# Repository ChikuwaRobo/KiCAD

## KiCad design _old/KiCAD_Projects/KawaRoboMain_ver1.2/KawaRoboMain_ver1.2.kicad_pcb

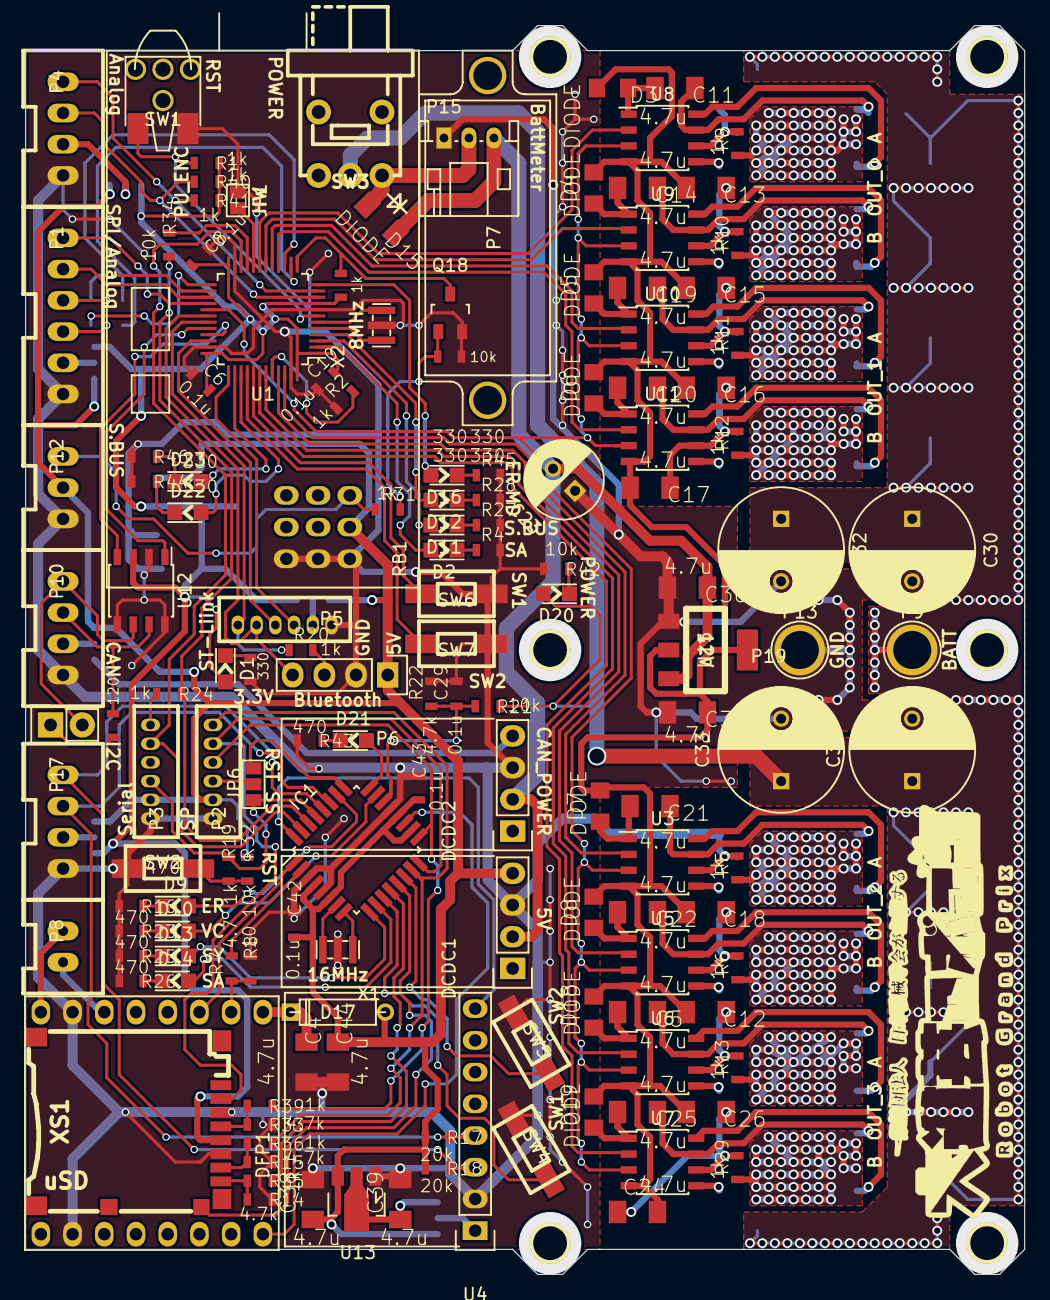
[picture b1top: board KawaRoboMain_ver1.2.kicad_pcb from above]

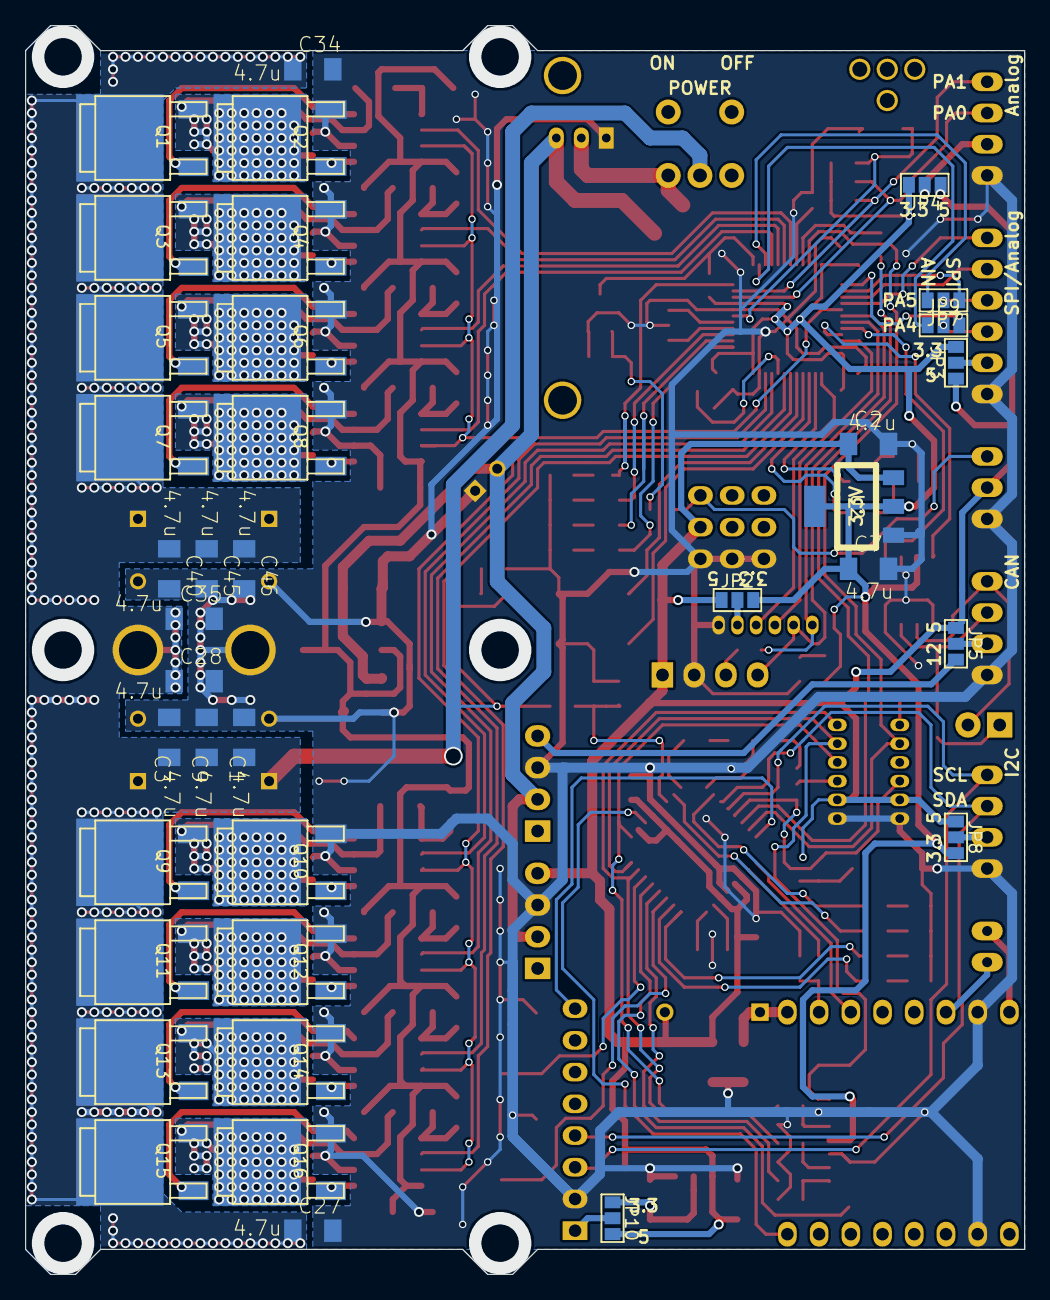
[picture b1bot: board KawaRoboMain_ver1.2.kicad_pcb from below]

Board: 2 copper layers, 80.0 x 100.0 mm, 189 parts (37 on the bottom side), 141 nets.

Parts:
C1, C2, C3, C4, C5, C7, C9, C11, C12, C13, C14, C15, C16, C17, C18, C19, C20, C21, C22, C24, C25, C26, C27, C28, C34, C35, C36, C37, C38, C39, C40, C44, C45, C46: 4.7u; C3216_S
C6, C8, C10, C29, C42, C43: 0.1u; C1608_WP_S
C23: C; C_Radial_D6.3_L11.2_P2.5
C30, C31, C32, C33: 220u; C_Radial_D10_L13_P5
D1, D2, D9, D10, D11, D12, D13, D14, D16, D20, D21, D22, D23: LED; LED_0805
D3, D4, D5, D6, D7, D8, D18, D19: DIODE; C2012
D15: DIODE; C3216_S
D17: DIODE; D3
DCDC1, DCDC2: ChinaDC-DC
DFP1: DFPlayerMini; DFPlayer
IC1: ATMEGA328P-A; TQFP-32_7x7mm_Pitch0.8mm
JP1: JUMPER; GS2
JP2, JP3, JP4, JP5, JP6, JP7, JP8, JP9, JP10: JUMPER3; GS3
P1: CONN_01X06; XA_6T
P2, P3, P5: CONN_01X06; ZH_6T
P4, P10, P17: CONN_01X04; XA_4T
P6: CONN_01X04; Socket_Strip_Straight_1x04
P7: CONN_01X01; V_BattMeter
P8: CONN_01X02; XA_2T
P9, P13: CONN_01X01; 1pin
P11: CONN_01X02; Pin_Header_Straight_1x02
P12: CONN_01X03; XA_3T
P14: CONN_01X01; RGP_R_N
P15: CONN_01X03; Connectors_JST_S3B-PH-K
P19: CONN_01X01; KawaRobo_Headsink_95x35
P21: CONN_01X01; kw_31mm
P22: CONN_01X01; RGP_S_D
Q1, Q2, Q3, Q4, Q5, Q6, Q7, Q8, Q9, Q10, Q11, Q12, Q13, Q14, Q15, Q16: MOSFET_N; SOT-428_GDS_compact
Q18: MOSFET_N; SOT-23_Handsoldering
R1, R2, R5, R6, R9, R10, R11, R12, R13, R19, R20, R24, R29, R31, R35, R36, R38, R39, R40, R41: 1k; C1608_WP_S
R3, R4, R27, R28, R44, R45, R46: 330; C1608_WP_S
R7: 4.7; C1608_WP_S
R8: 10; C1608_WP_S
R14, R15, R22, R33: 4.7k; C1608_WP_S
R16, R23, R25, R26, R43: 470; C1608_WP_S
R17, R18: 20k; C1608_WP_S
R21, R32, R34, R37, R42: 10k; C1608_WP_S
R30: 120; C1608_WP_S
RB1: R3006SB
SW1: SW_PUSH; ESE22MH
SW2, SW4, SW5, SW6, SW7: SW_PUSH; RP_SMD_Button
SW3: SWITCH_INV; RSpro_slide_side
U1: STM32F103_48; LQFP-48_7x7mm_Pitch0.5mm
U2: NCP1117ST33T3G; SOT-223_reg
U3, U5, U6, U7, U8, U9, U10, U11: NCP5359; SOIC-8_3.9x4.9mm_Pitch1.27mm_S
U4: MPU6050; MPU-6050
U12: MAX3051; SOIC-8_3.9x4.9mm_Pitch1.27mm_S
U13: NCP1117ST33T3G; SOT89-3_Housing
U15: NCP1117ST12T3G; SOT-223_reg
X1, X2: ceralock; Resonator_3×1.3mm
XS1: uSD; microsd_socket

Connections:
+3.3V: C6.2, C7.1, C8.2, C10.2, D1.1, JP2.3, JP3.3, JP4.3, JP8.3, R1.1, R38.2, R40.1, R41.1, U1.1, U1.9, U1.24, U1.36, U1.48, U2.2, U12.3, XS1.4
+5V: C2.1, C38.1, C42.2, C43.2, C44.1, D17.2, DCDC1.4, IC1.4, IC1.6, IC1.18, IC1.20, JP2.1, JP3.1, JP4.1, JP5.1, JP8.1, JP10.3, P2.2, P3.2, P6.1, P12.2, R17.2, R18.2, R32.1, RB1.2, U2.3, U13.3
+12V: DCDC2.4, JP5.3
+BATT: C1.1, C3.1, C9.1, C27.1, C28.1, C30.1, C31.1, C32.1, C33.1, C34.1, C35.1, C40.1, C45.1, C46.1, D20.1, P9.1, Q1.D, Q3.D, Q5.D, Q7.D, Q9.D, Q11.D, Q13.D, Q15.D, R21.1, SW3.2
/AIN_1: JP9.1, U1.14
/AIN_2: JP7.3, U1.15
/AT_LED1: D13.1, IC1.9
/AT_LED2: D14.1, IC1.10
/AT_LED3: D9.1, IC1.26
/AT_LED4: D10.1, IC1.23
/AT_LED5: D21.1, IC1.24
/AT_RST: IC1.29, JP6.1, P3.3, R19.1
/AT_RX: IC1.30, R24.1, R34.2
/AT_SW1: IC1.11, SW4.2
/AT_SW2: IC1.14, SW5.2
/AT_TX: IC1.31, P3.5, U1.22
/BOOT0: R2.2, U1.44
/CAN_H: P10.3, R30.1, U12.7
/CAN_L: P10.4, P11.2, U12.6
/CAN_RX: U1.33, U12.4
/CAN_TX: U1.32, U12.1
/DFP_BUSY: DFP1.16, IC1.19
/DFP_RX: IC1.2, R7.2
/DFP_TX: DFP1.3, IC1.1
/EX_SS: IC1.25, JP6.3
/GD_12V: C12.2, C13.2, C15.2, C16.2, C17.2, C18.2, C24.2, C26.2, C37.1, D3.2, D4.2, D5.2, D6.2, D7.2, D8.2, D18.2, D19.2, U3.4, U5.4, U6.4, U7.4, U8.4, U9.4, U10.4, U11.4, U15.2
/HW_OPT: JP1.2, U1.20
/I2C_SCL: IC1.28, P17.4, R18.1, U4.3
/I2C_SDA: IC1.27, P17.3, R17.1, U4.4
/INT0: IC1.32, U4.8
/LOGIC_BATT: C23.2, C36.1, D15.1, DCDC1.2, DCDC2.2, P15.3, U15.3
/MPU_3.3V: C39.1, JP10.1, U13.2
/NRST: R1.2, SW1.2, U1.7
/OSC_IN: U1.5, X2.1
/OSC_OUT: U1.6, X2.3
/OUT_0_A: C11.1, Q1.S, Q2.D, R9.1, U8.7
/OUT_0_B: C14.1, Q3.S, Q4.D, R10.1, U9.7
/OUT_1_A: C19.1, Q5.S, Q6.D, R11.1, U10.7
/OUT_1_B: C20.1, Q7.S, Q8.D, R12.1, U11.7
/OUT_2_A: C21.1, Q9.S, Q10.D, R5.1, U3.7
/OUT_2_B: C22.1, Q11.S, Q12.D, R6.1, U5.7
/OUT_3_A: C5.1, Q13.S, Q14.D, R13.1, U6.7
/OUT_3_B: C25.1, Q15.S, Q16.D, R29.1, U7.7
/POT_1: P4.3, R40.2, U1.10
/POT_2: P4.4, R41.2, U1.11
/PWM_0_A: U1.19, U8.2
/PWM_0_B: U1.18, U9.2
/PWM_1_A: U1.17, U10.2
/PWM_1_B: U1.16, U11.2
/PWM_2_A: U1.46, U3.2
/PWM_2_B: U1.45, U5.2
/PWM_3_A: U1.43, U6.2
/PWM_3_B: U1.42, U7.2
/SBUS: Q18.D, R38.1, U1.13
/SD_CD: IC1.13, XS1.CD2
/SD_SS: IC1.12, R35.1
/SPI_MISO: IC1.16, P2.5, XS1.7
/SPI_MOSI: IC1.15, P2.6, R36.1
/SPI_SCK: IC1.17, P2.4, R39.1
/STM_LED1: D2.1, U1.2
/STM_LED2: D11.1, U1.3
/STM_LED3: D12.1, U1.4
/STM_LED4: D16.1, U1.12
/STM_LED5: D22.1, U1.39
/STM_LED6: D23.1, U1.38
/STM_MISO: P1.5, U1.27
/STM_MOSI: P1.6, U1.28
/STM_SCK: JP7.1, U1.26
/STM_SW1: SW6.2, U1.41
/STM_SW2: SW7.2, U1.40
/STM_~SS0: JP9.3, U1.25
/SWCLK: P5.3, U1.37
/SWDIO: P5.4, U1.34
/USART_RX: P5.6, R20.1, U1.31
/USART_TX: P5.5, P6.4, U1.30
/batt_voltage: C29.1, IC1.22, R21.2, R22.1
/~SD: U1.29, U3.3, U5.3, U6.3, U7.3, U8.3, U9.3, U10.3, U11.3
GND: C1.2, C2.2, C3.2, C4.2, C6.1, C7.2, C8.1, C9.2, C10.1, C12.1, C13.1, C15.1, C16.1, C17.1, C18.1, C23.1, C24.1, C26.1, C27.2, C28.2, C29.2, C30.2, C31.2, C32.2, C33.2, C34.2, C35.2, C36.2, C37.2, C38.2, C39.2, C40.2, C42.1, C43.1, C44.2, C45.2, C46.2, DCDC1.3, DCDC2.3, DFP1.7, DFP1.10, IC1.3, IC1.5, IC1.21, JP1.1, P1.1, P2.1, P3.1, P4.1, P5.1, P6.2, P10.1, P12.1, P13.1, P15.1, P17.1, Q2.S, Q4.S, Q6.S, Q8.S, Q10.S, Q12.S, Q14.S, Q16.S, Q18.S, R2.1, R3.2, R4.2, R5.2, R6.2, R8.1, R9.2, R10.2, R11.2, R12.2, R13.2, R14.1, R15.1, R16.2, R22.2, R23.2, R25.2, R26.2, R27.2, R28.2, R29.2, R33.1, R37.1, R42.2, R43.2, R44.2, R45.2, R46.2, RB1.1, RB1.4, RB1.7, SW1.1, SW2.1, SW4.1, SW5.1, SW6.1, SW7.1, U1.8, U1.23, U1.35, U1.47, U2.1, U3.6, U4.2, U5.6, U6.6, U7.6, U8.6, U9.6, U10.6, U11.6, U12.2, U12.5, U12.8, U13.1, U15.1, X1.2, X2.2, XS1.3, XS1.6
unnamed: C4.1, D17.1, DFP1.1
unnamed: C5.2, D18.1, U6.1
unnamed: C11.2, D3.1, U8.1
unnamed: C14.2, D4.1, U9.1
unnamed: C19.2, D5.1, U10.1
unnamed: C20.2, D6.1, U11.1
unnamed: C21.2, D7.1, U3.1
unnamed: C22.2, D8.1, U5.1
unnamed: C25.2, D19.1, U7.1
unnamed: D1.2, R3.1
unnamed: D2.2, R4.1
unnamed: D9.2, R16.1
unnamed: D10.2, R23.1
unnamed: D11.2, R27.1
unnamed: D12.2, R28.1
unnamed: D13.2, R25.1
unnamed: D14.2, R26.1
unnamed: D15.2, P15.2, SW3.3
unnamed: D16.2, R45.1
unnamed: D20.2, R42.1
unnamed: D21.2, R43.1
unnamed: D22.2, R44.1
unnamed: D23.2, R46.1
unnamed: DFP1.2, R7.1, R8.2
unnamed: DFP1.6, P8.1
unnamed: DFP1.8, P8.2
unnamed: IC1.7, X1.3
unnamed: IC1.8, X1.1
unnamed: JP2.2, P5.2
unnamed: JP3.2, P1.2
unnamed: JP4.2, P4.2
unnamed: JP5.2, P10.2
unnamed: JP6.2, P2.3
unnamed: JP7.2, P1.4
unnamed: JP8.2, P17.2
unnamed: JP9.2, P1.3
unnamed: JP10.2, U4.1
unnamed: P3.6, R24.2
unnamed: P6.3, R20.2
unnamed: P11.1, R30.2
unnamed: P12.3, R31.1, RB1.3
unnamed: Q1.G, U8.8
unnamed: Q2.G, U8.5
unnamed: Q3.G, U9.8
unnamed: Q4.G, U9.5
unnamed: Q5.G, U10.8
unnamed: Q6.G, U10.5
unnamed: Q7.G, U11.8
unnamed: Q8.G, U11.5
unnamed: Q9.G, U3.8
unnamed: Q10.G, U3.5
unnamed: Q11.G, U5.8
unnamed: Q12.G, U5.5
unnamed: Q13.G, U6.8
unnamed: Q14.G, U6.5
unnamed: Q15.G, U7.8
unnamed: Q16.G, U7.5
unnamed: Q18.G, R31.2, R37.2
unnamed: R14.2, R35.2, XS1.1
unnamed: R15.2, R36.2, XS1.2
unnamed: R19.2, R32.2, SW2.2
unnamed: R33.2, R39.2, XS1.5
unnamed: R34.1, U1.21

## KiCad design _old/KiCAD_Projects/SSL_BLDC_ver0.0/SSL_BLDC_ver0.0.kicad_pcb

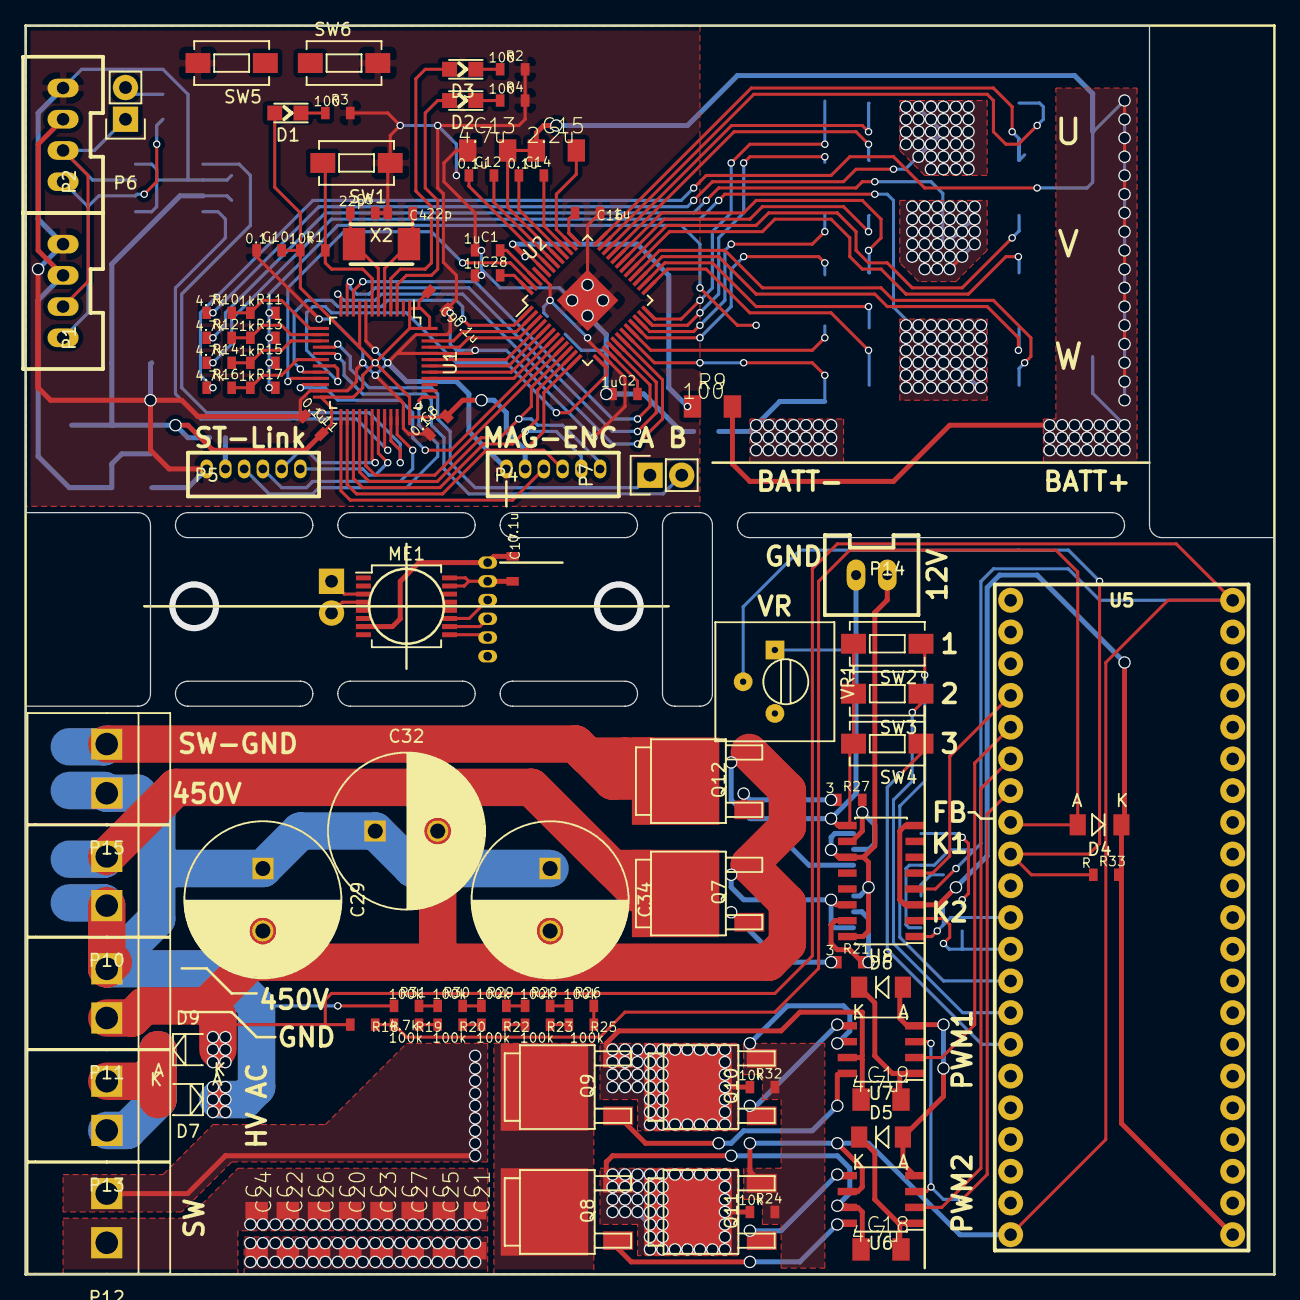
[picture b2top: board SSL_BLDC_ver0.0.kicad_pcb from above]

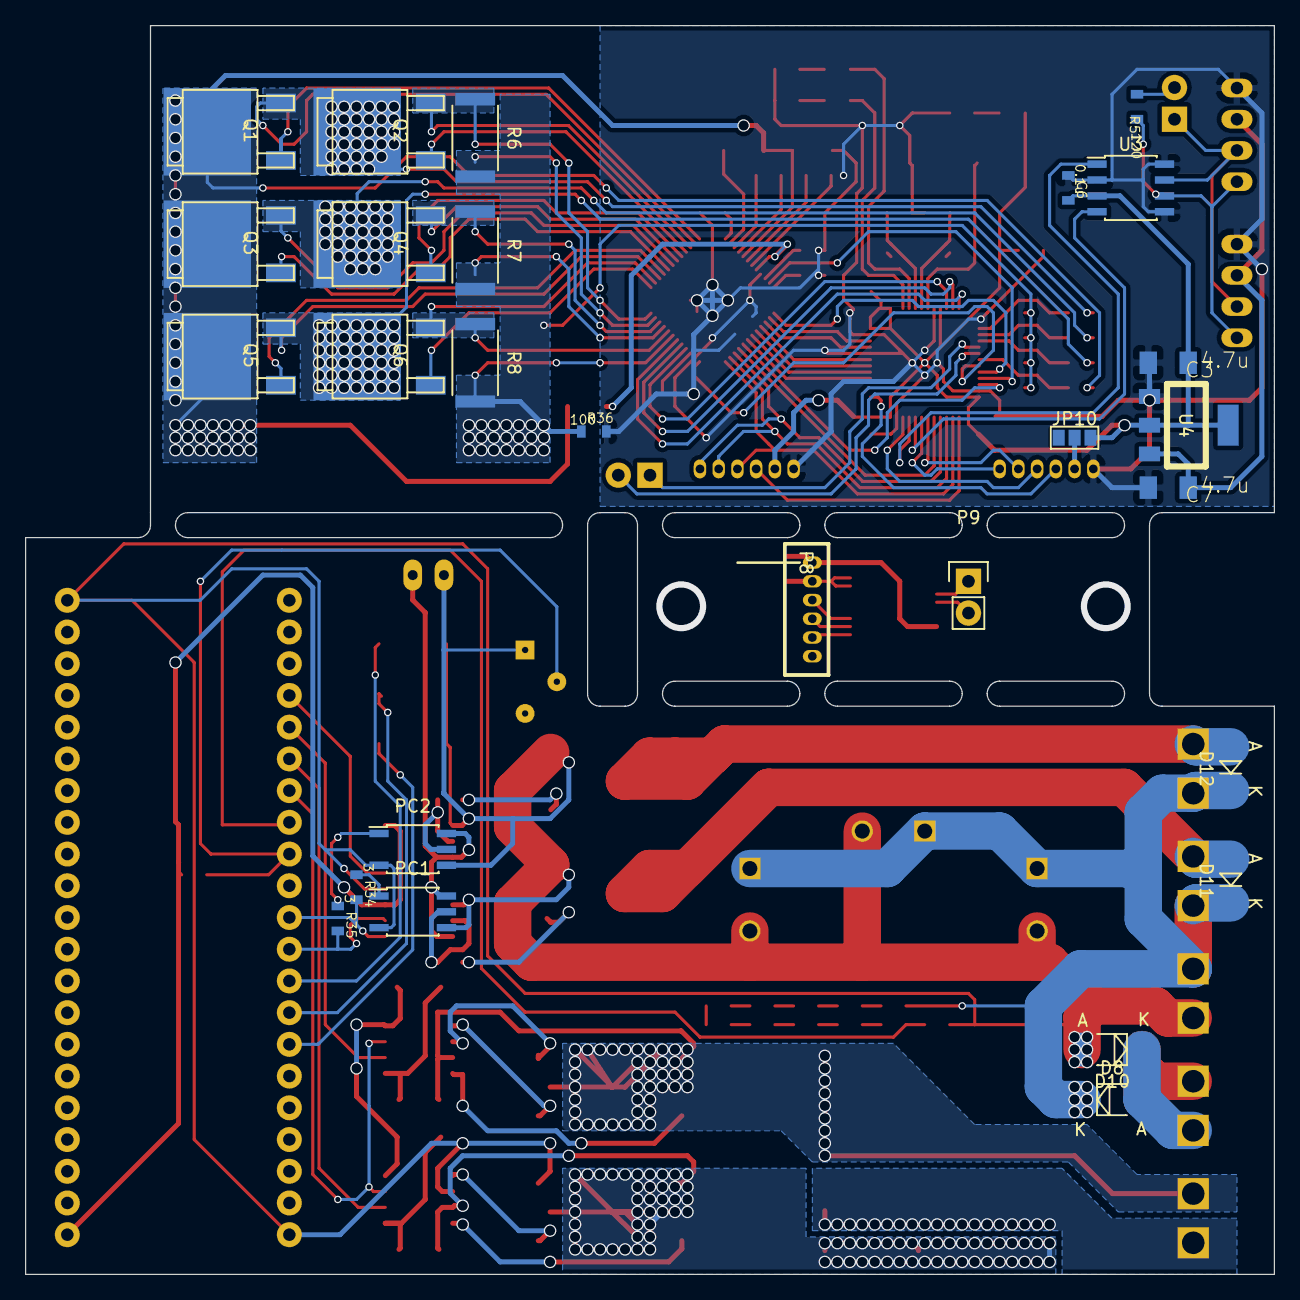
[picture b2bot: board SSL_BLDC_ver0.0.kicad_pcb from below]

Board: 2 copper layers, 100.0 x 100.0 mm, 125 parts (27 on the bottom side), 123 nets.

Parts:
C1, C2, C16, C28: 1u; C1608_WP_S
C3, C7, C13, C18, C19: 4.7u; C3216_S
C4, C5: 22p; C1608_WP_S
C6, C8, C9, C10, C11, C12, C14, C17: 0.1u; C1608_WP_S
C15: 2.2u; C3216_S
C20, C21, C22, C23, C24, C25, C26, C27: C; C3216_S
C29, C32, C34: C; C_Radial_D12.5_L25_P5
D1, D2, D3: LED; LED_0805
D4, D5, D6, D11, D12: DIODE; MiniMELF_Standard
D7, D8, D9, D10: DIODE; MELF_Standard
JP10: JUMPER3; GS3
ME1: AS504x; SSOP-16_5.3x6.2mm_Pitch0.65mm
P1, P2: CONN_01X04; XA_4T
P4, P5, P8: CONN_01X06; ZH_6T
P6, P7, P9: CONN_01X02; Pin_Header_Straight_1x02
P10, P11, P12, P13, P15: CONN_01X02; GTK2400-V2
P14: CONN_01X02; XA_2T
PC1, PC2: TLP117; SOIC-5_3.9x4.9mm_Pitch1.27mm
Q1, Q2, Q3, Q4, Q5, Q6, Q7, Q8, Q9, Q10, Q11, Q12: MOSFET_N; SOT-428_GDS_compact
R1, R24, R32: 10k; C1608_WP_S
R2, R3, R4, R36: 100; C1608_WP_S
R5: 120; C1608_WP_S
R6, R7, R8: 10m; R_2512
R9: 100; C3216_S
R10, R12, R14, R16, R18: 4.7k; C1608_WP_S
R11, R13, R15, R17: 1k; C1608_WP_S
R19, R20, R22, R23, R25, R26, R28, R29, R30, R31: 100k; C1608_WP_S
R21, R27, R34, R35: 3; C1608_WP_S
R33: R; C1608_WP_S
SW1, SW2, SW3, SW4, SW5, SW6: SW_PUSH; SW_SPST_EVQPE1
U1: STM32F103_48; LQFP-48_7x7mm_Pitch0.5mm
U2: DRV8305; TQFP-48-1EP_7x7mm_Pitch0.5mm
U3: MAX3051; SOIC-8_3.9x4.9mm_Pitch1.27mm
U4: NCP1117ST50T3G; SOT-223_reg
U5: F103mini_Ver2.0; F103mini_ver2.0
U6, U7: NCP5359; SOIC-8_3.9x4.9mm_Pitch1.27mm
U8: SI8275; SOIC-16_3.9x9.9mm_Pitch1.27mm
VR1: VR; Potentiometer_Trimmer-Suntan-TSR-3386P
X2: CRYSTAL; ABM3_2pads

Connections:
+3.3V: C3.1, C6.2, C8.2, C9.2, C10.2, C11.2, D1.1, JP10.3, P4.2, R1.1, U1.1, U1.9, U1.24, U1.36, U1.48, U3.3, U4.2
+3.3VP: D4.1, R33.2, U5.22, U8.3, U8.8
+5V: C7.1, P1.2, P2.2, U4.3
+12V: D5.2, D6.2, U6.4, U7.4
+BATT: C13.2, C15.1, Q1.D, Q3.D, Q5.D, R9.2, R16.1, U2.41
/AS_3.3V: C17.2, ME1.15, ME1.16, P8.2
/AS_ENC_A: ME1.3, P9.1
/AS_ENC_B: ME1.4, P9.2
/AS_GND: C17.1, ME1.7, P8.1
/AS_SPI_MISO: ME1.9, P8.5
/AS_SPI_NSS_ENC: ME1.11, P8.3
/AS_SPI_SCK: ME1.10, P8.4
/BATT_V: R16.2, R17.1, U1.18
/CAN_H: P1.3, P2.3, P6.1, U3.7
/CAN_L: P1.4, P2.4, R5.1, U3.6
/CAN_RX: U1.32, U3.4
/CAN_TX: U1.33, U3.1
/CS_U: U1.10, U2.16
/CS_V: U1.11, U2.17
/CS_W: U1.12, U2.18
/ENC_A: P7.1, U1.16
/ENC_B: P7.2, U1.17
/GATE_U_H: Q1.G, U2.36
/GATE_U_L: Q2.G, U2.33
/GATE_V_H: Q3.G, U2.29
/GATE_V_L: Q4.G, U2.32
/GATE_W_H: Q5.G, U2.28
/GATE_W_L: Q6.G, U2.25
/GD_EN: U1.20, U2.1
/GD_WAKE: U1.21, U2.47
/LED_A: D2.1, U1.3
/LED_B: D3.1, U1.4
/NRST: R1.2, SW1.2, U1.7
/OSC_IN: C4.1, U1.5, X2.1
/OSC_OUT: C5.1, U1.6, X2.2
/OUT_U: Q1.S, Q2.D, R10.1, U2.35
/OUT_V: Q3.S, Q4.D, R12.1, U2.30
/OUT_W: Q5.S, Q6.D, R14.1, U2.27
/PWGD: U1.19, U2.13
/PWM_U_H: U1.46, U2.2
/PWM_U_L: U1.45, U2.3
/PWM_V_H: U1.43, U2.4
/PWM_V_L: U1.42, U2.5
/PWM_W_H: U1.41, U2.6
/PWM_W_L: U1.40, U2.7
/SPI_MISO: P4.5, U1.27, U2.11
/SPI_MOSI: P4.6, U1.28, U2.10
/SPI_NSS_ENC: P4.3, U1.25
/SPI_NSS_GD: U1.29, U2.9
/SPI_SCK: P4.4, U1.26, U2.12
/SWCLK: P5.3, U1.37
/SWDIO: P5.4, U1.34
/S_U_L: Q2.S, R6.1, U2.24, U2.34
/S_V_L: Q4.S, R7.1, U2.22, U2.31
/S_W_L: Q6.S, R8.1, U2.20, U2.26
/USART_RX: P5.6, U1.31
/USART_TX: P5.5, U1.30
/VS_U: R10.2, R11.1, U1.13
/VS_V: R12.2, R13.1, U1.14
/VS_W: R14.2, R15.1, U1.15
/boost/450V: C29.1, C32.1, C34.1, D7.1, D8.1, D11.1, D12.1, P10.1, P11.2, P15.1, R31.1
/boost/FB: D4.2, R18.1, R19.2, U5.8
/boost/GD_EN: U5.4, U8.5
/boost/GD_EN_NCP: U5.7, U6.3, U7.3
/boost/GD_PWM1: U5.5, U7.2
/boost/GD_PWM2: U5.6, U6.2
/boost/KICK_GATE1: PC1.5, R21.2, U8.15
/boost/KICK_GATE2: PC2.5, R27.2, U8.10
/boost/Kick1: R34.2, U5.11, U8.1
/boost/Kick2: R35.2, U5.12, U8.2
/boost/SW1: C19.1, P12.2, Q9.S, Q10.D, R32.1, U7.7
/boost/SW2: C20.1, C21.1, C22.1, C23.1, C24.1, C25.1, C26.1, C27.1, P12.1
/boost/analog: R33.1, U5.9, VR1.2
/boost/boostBATT: Q8.D, Q9.D
/boost/pw12V: P14.2, PC1.6, PC2.6, U8.11, U8.16
/boost/userSW1: SW2.1, U5.13
/boost/userSW2: SW3.1, U5.14
/boost/userSW3: SW4.1, U5.15
/nFALUT: U1.22, U2.8
DGND: C29.2, C32.2, C34.2, D9.2, D10.2, P11.1, P14.1, PC1.3, PC1.4, PC2.3, PC2.4, Q7.S, Q10.S, Q11.S, Q12.S, R18.2, R24.2, R32.2, SW2.2, SW3.2, SW4.2, U5.21, U5.42, U6.6, U7.6, U8.4, U8.9, U8.14, VR1.1
GND: C1.1, C2.1, C3.2, C4.2, C5.2, C6.1, C7.2, C8.1, C9.1, C10.1, C11.1, C13.1, C16.1, C28.1, P1.1, P2.1, P4.1, P5.1, R2.2, R3.2, R4.2, R36.2, SW1.1, SW5.2, SW6.2, U1.8, U1.23, U1.35, U1.44, U1.47, U2.14, U2.45, U2.49, U3.2, U3.5, U3.8, U4.1
GNDPWR: R6.2, R7.2, R8.2, R11.2, R13.2, R15.2, R17.2, R36.1, U2.19, U2.21, U2.23
unnamed: C1.2, U2.46
unnamed: C2.2, U2.15
unnamed: C12.1, U2.43
unnamed: C12.2, U2.42
unnamed: C14.1, U2.40
unnamed: C14.2, U2.39
unnamed: C15.2, U2.38
unnamed: C16.2, U2.37
unnamed: C18.1, C20.2, C21.2, C22.2, C23.2, C24.2, C25.2, C26.2, C27.2, Q8.S, Q11.D, R24.1, U6.7
unnamed: C18.2, D5.1, U6.1
unnamed: C19.2, D6.1, U7.1
unnamed: C28.2, U2.48
unnamed: D1.2, R3.1
unnamed: D2.2, R4.1
unnamed: D3.2, R2.1
unnamed: D7.2, D9.1, P13.2
unnamed: D8.2, D10.1, P13.1
unnamed: D11.2, P10.2, Q7.D
unnamed: D12.2, P15.2, Q12.D
unnamed: JP10.2, P5.2
unnamed: P6.2, R5.2
unnamed: PC1.1, R34.1
unnamed: PC2.1, R35.1
unnamed: Q7.G, R21.1
unnamed: Q8.G, U6.8
unnamed: Q9.G, U7.8
unnamed: Q10.G, U7.5
unnamed: Q11.G, U6.5
unnamed: Q12.G, R27.1
unnamed: R9.1, U2.44
unnamed: R19.1, R20.2
unnamed: R20.1, R22.2
unnamed: R22.1, R23.2
unnamed: R23.1, R25.2
unnamed: R25.1, R26.2
unnamed: R26.1, R28.2
unnamed: R28.1, R29.2
unnamed: R29.1, R30.2
unnamed: R30.1, R31.2
unnamed: SW5.1, U1.39
unnamed: SW6.1, U1.38

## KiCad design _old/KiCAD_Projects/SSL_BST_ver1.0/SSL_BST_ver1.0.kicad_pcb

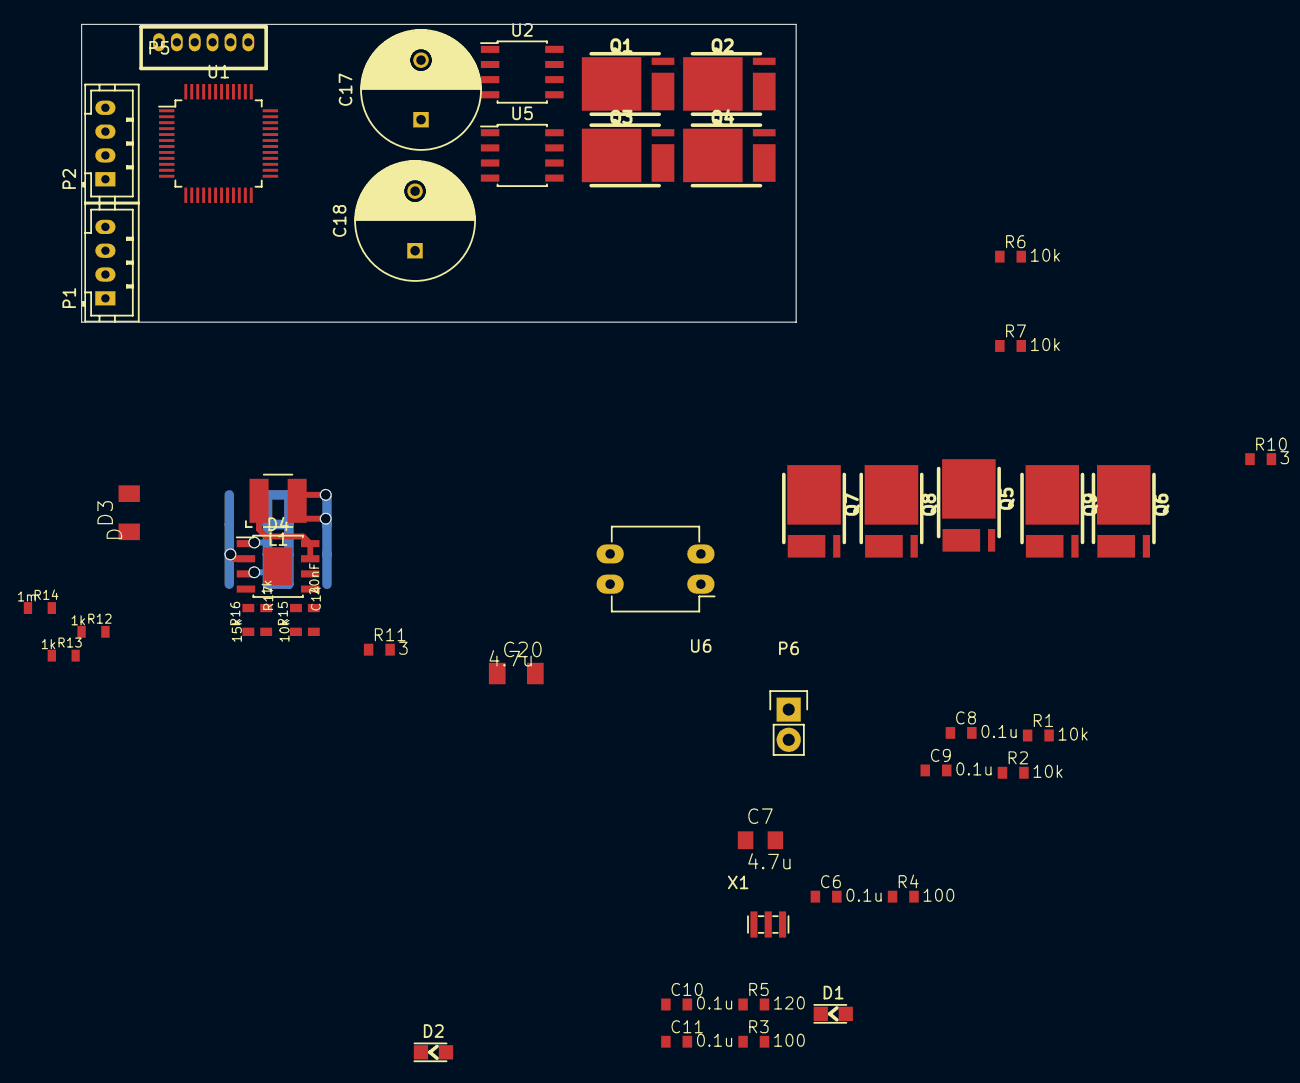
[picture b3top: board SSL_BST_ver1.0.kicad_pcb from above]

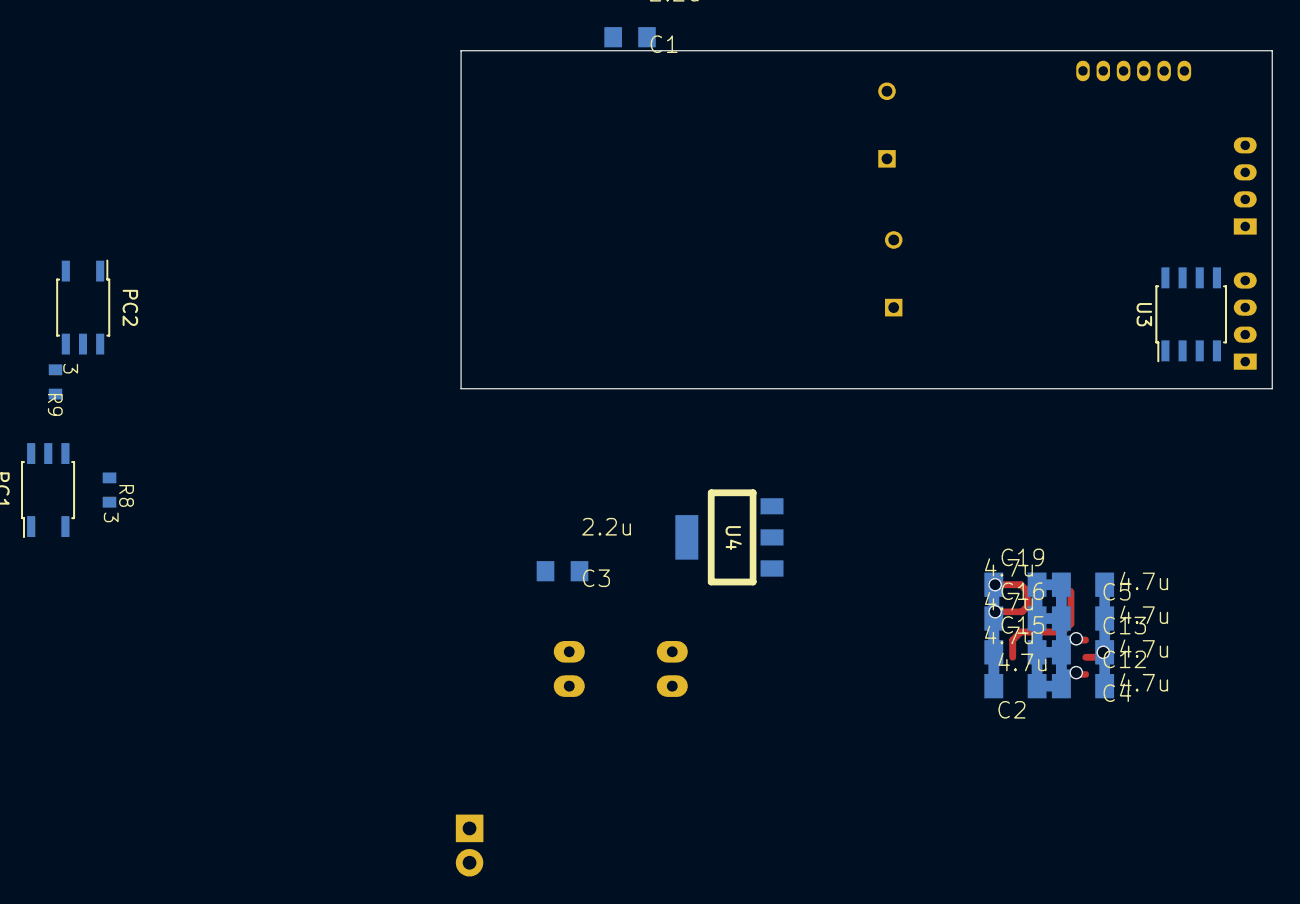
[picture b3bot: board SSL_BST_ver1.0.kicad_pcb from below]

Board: 2 copper layers, 60.0 x 25.0 mm, 64 parts (16 on the bottom side), 42 nets.

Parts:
C1, C3: 2.2u; C2012
C2, C4, C5, C12, C13, C15, C16, C19, C20: 4.7u; C3216_S
C6, C8, C9, C10, C11: 0.1u; C1608_WP
C7: 4.7u; C2012
C14: 20nF; C1608_WP_S
C17, C18: 470u; C_Radial_D10_L13_P5
D1, D2: LED; LED_0805
D3: D; C3216_S
D4: BD9C601EFJ; SOIC-8_3.9x4.9mm_Pitch1.27mm
L1: 3.3uH; NR4018
P1, P2: CONN_01X04; Connectors_JST_B4B-PH-K
P5: CONN_01X06; ZH_6T
P6: CONN_01X02; Pin_Header_Straight_1x02
PC1, PC2: TLP117; SOIC-5_3.9x4.9mm_Pitch1.27mm
Q1, Q2, Q3, Q4, Q5: Q_NMOS_GDS; DFN56
Q6, Q7, Q8, Q9: Q_PMOS_GDS; DFN56
R1, R2, R6, R7: 10k; C1608_WP
R3, R4: 100; C1608_WP
R5: 120; C1608_WP
R8, R9, R10, R11: 3; C1608_WP
R12, R13, R17: 1k; C1608_WP_S
R14: 1m; C1608_WP_S
R15: 10k; C1608_WP_S
R16: 15k; C1608_WP_S
U1: STM32F103_48; LQFP-48_7x7mm_Pitch0.5mm
U2, U5: NCP5359; SOIC-8_3.9x4.9mm_Pitch1.27mm
U3: MAX3051; SOIC-8_3.9x4.9mm_Pitch1.27mm
U4: NCP1117ST50T3G; SOT-223_reg
U6: OPTO-TRANSISTOR4; DIP-4_W7.62mm_LongPads
X1: ceralock; Resonator_3×1.3mm

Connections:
+3.3V: C6.2, C7.1, C8.2, C9.2, C10.2, D1.1, R1.1, U1.9, U1.24, U1.36, U1.48, U3.3, U4.2
+12V: C2.1, C15.1, C16.1, C19.1, C20.1, L1.2, R16.1, U2.1, U2.4, U4.3, U5.1, U5.4
+BATT: D3.2, R12.2, R14.2
/BOOT0: R2.2, U1.44
/CAN_H: P1.3, P2.3, P6.1, U3.7
/CAN_L: P1.4, P2.4, R5.1, U3.6
/CAN_RX: U1.32, U3.4
/CAN_TX: U1.33, U3.1
/CS_N: Q6.3, Q7.3, Q8.3, Q9.3, R14.1
/GD_12V: PC1.6, PC2.6
/NCP_EN: U2.3, U5.3
/NRST: R1.2, U1.7
/OSC_IN: U1.5, X1.1
/OSC_OUT: U1.6, X1.3
/OUT_EN: Q5.1, R13.2
/PW_OUT: C17.1, C18.1, Q1.2, Q3.2, Q6.2, Q7.2, Q8.2, Q9.2
/SW1: Q1.3, Q2.2, R6.1, U2.7
/SWCLK: P5.3, U1.37
/SWDIO: P5.4, U1.34
/USART_RX: P5.6, U1.31
/USART_TX: P5.5, U1.30
GND: C2.2, C4.2, C5.2, C6.1, C7.2, C8.1, C9.1, C10.1, C11.1, C12.2, C13.2, C14.2, C15.2, C16.2, C19.2, C20.2, D4.1, D4.3, P1.1, P2.1, P5.1, PC1.3, PC2.3, Q2.3, Q4.3, Q5.3, R3.2, R4.2, R6.2, R7.2, R13.1, R17.2, U1.8, U1.23, U1.35, U2.6, U3.2, U3.5, U3.8, U4.1, U5.6, X1.2
GNDPWR: C17.2, C18.2, PC1.4, PC2.4
unnamed: C4.1, C5.1, C12.1, C13.1, D3.1, D4.2
unnamed: C14.1, R15.1
unnamed: D1.2, R3.1
unnamed: D2.2, R4.1
unnamed: D4.4, R16.2, R17.1
unnamed: D4.5, R15.2
unnamed: D4.7, D4.8, L1.1
unnamed: P1.2, P2.2
unnamed: P6.2, R5.2
unnamed: PC1.1, R10.1
unnamed: PC1.5, R8.2
unnamed: PC2.1, R11.1
unnamed: PC2.5, R9.2
unnamed: Q1.1, U2.8
unnamed: Q2.1, U2.5
unnamed: Q3.1, U5.8
unnamed: Q3.3, Q4.2, R7.1, U5.7
unnamed: Q4.1, U5.5
unnamed: Q5.2, Q6.1, Q7.1, Q8.1, Q9.1, R12.1

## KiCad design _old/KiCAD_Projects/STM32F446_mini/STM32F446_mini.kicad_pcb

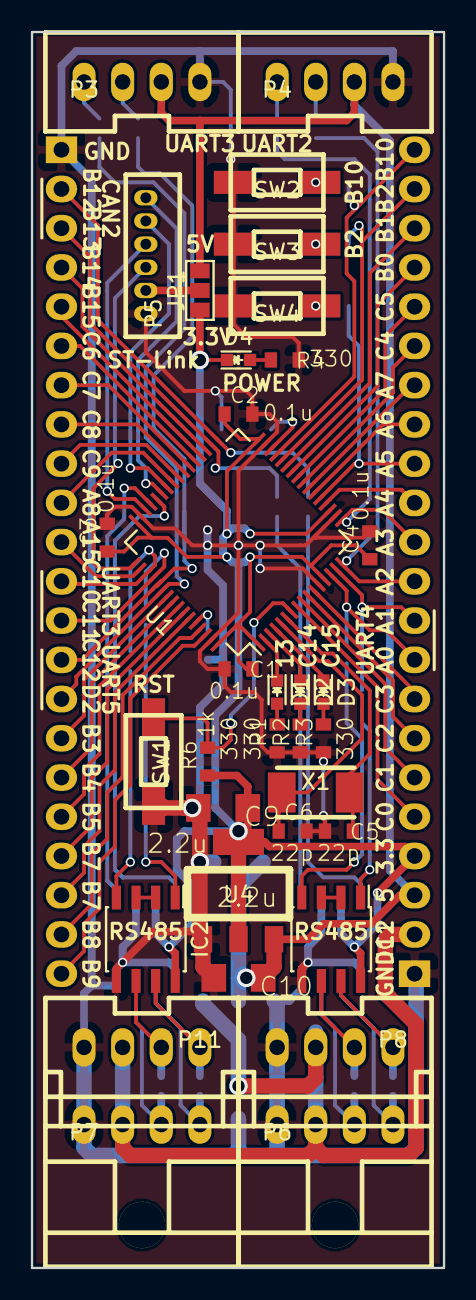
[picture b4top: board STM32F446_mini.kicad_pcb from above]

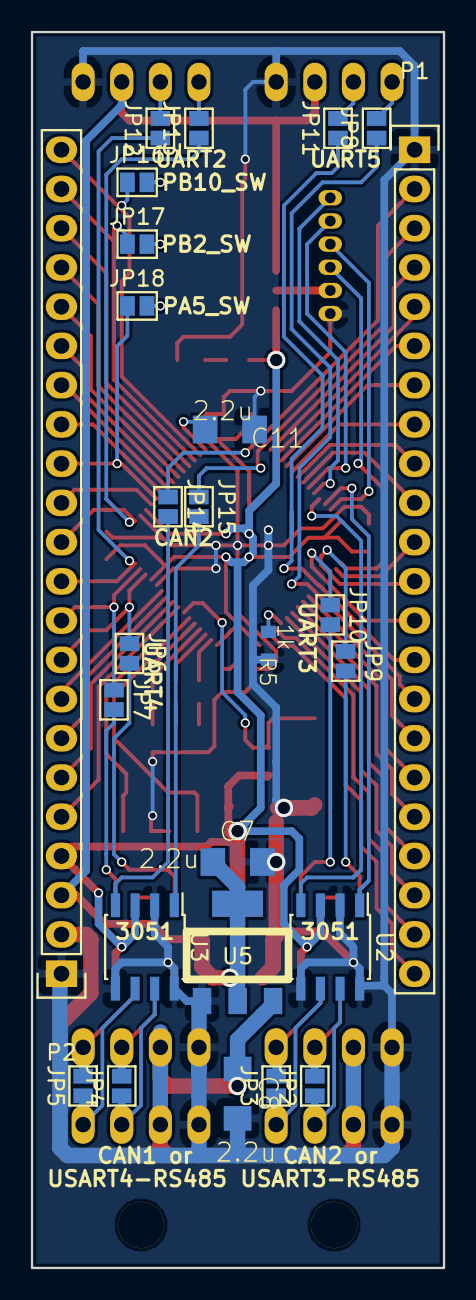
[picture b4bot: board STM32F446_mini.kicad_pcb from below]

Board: 2 copper layers, 26.7 x 80.0 mm, 60 parts (26 on the bottom side), 85 nets.

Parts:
C1, C2, C3, C4: 0.1u; C1608_WP
C5, C6: 22p; C1608_WP
C7, C8, C9, C10, C11: 2.2u; C3216
D1, D2, D3, D4: LED; LED_0603
IC1, IC2: SP3485CN; SOIC-8_3.9x4.9mm_Pitch1.27mm
JP1: JUMPER3; GS3
JP2, JP3, JP4, JP5, JP6, JP7, JP8, JP9, JP10, JP11, JP12, JP13, JP14, JP15, JP16, JP17, JP18: JUMPER; GS2
P1, P2: CONN_01X22; Pin_Header_Straight_1x22
P3, P4, P8, P11: CONN_01X04; XA_4T
P5: CONN_01X06; ZH_6T
P6, P7: CONN_01X04; XA_4LC
R1, R2, R3, R4: 330; C1608_WP
R5, R6: 1k; C1608_WP
SW1, SW2, SW3, SW4: SW_PUSH; RP_SMD_Button
U1: STM32F446RETx; LQFP-64_10x10mm_Pitch0.5mm
U2, U3: MAX3051; SOIC-8_3.9x4.9mm_Pitch1.27mm
U4: NCP1117ST33T3G; SOT-223_reg
U5: NCP1117ST50T3G; SOT-223_reg
X1: CRYSTAL; ABM3_2pads

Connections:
+3.3V: C1.1, C2.1, C3.1, C4.1, C9.1, D4.1, IC1.8, IC2.8, JP1.1, P2.4, R6.1, U1.1, U1.13, U1.19, U1.32, U1.48, U1.64, U2.3, U3.3, U4.2
+5V: C7.1, C10.1, JP1.3, P2.3, P3.2, P4.2, U4.3, U5.2
+12V: C8.1, P2.2, P6.2, P7.2, P8.2, P11.2, U5.3
/BOOT0: R5.2, U1.60
/CAN1_RX: U1.44, U2.4
/CAN1_TX: U1.45, U2.1
/CAN2_RX: JP14.2, U3.4
/CAN2_TX: JP15.2, U3.1
/NRST: R6.2, SW1.1, U1.7
/PA0: JP6.1, P2.9, U1.14
/PA1: JP7.1, P2.10, U1.15
/PA2: JP12.1, P2.11, U1.16
/PA3: JP13.1, P2.12, U1.17
/PA4: P2.13, U1.20
/PA5: JP18.1, P2.14, U1.21
/PA6: P2.15, U1.22
/PA7: P2.16, U1.23
/PA8: P1.10, U1.41
/PA15: P1.11, U1.50
/PB0: P2.19, U1.26
/PB1: P2.20, U1.27
/PB2: JP17.1, P2.21, U1.28
/PB3: P1.16, U1.55
/PB4: P1.17, U1.56
/PB5: P1.18, U1.57
/PB6: P1.19, U1.58
/PB7: P1.20, U1.59
/PB8: P1.21, U1.61
/PB9: P1.22, U1.62
/PB10: JP16.1, P2.22, U1.29
/PB12: JP14.1, P1.2, U1.33
/PB13: JP15.1, P1.3, U1.34
/PB14: P1.4, U1.35
/PB15: P1.5, U1.36
/PC0: P2.5, U1.8
/PC1: P2.6, U1.9
/PC2: P2.7, U1.10
/PC3: P2.8, U1.11
/PC4: P2.17, U1.24
/PC5: P2.18, U1.25
/PC6: P1.6, U1.37
/PC7: P1.7, U1.38
/PC8: P1.8, U1.39
/PC9: P1.9, U1.40
/PC10: JP9.1, P1.12, U1.51
/PC11: JP10.1, P1.13, U1.52
/PC12: JP11.1, P1.14, U1.53
/PC13: D1.1, U1.2
/PC14: D2.1, U1.3
/PC15: D3.1, U1.4
/PD2: JP8.1, P1.15, U1.54
/PH0: C6.1, U1.5, X1.2
/PH1: C5.1, U1.6, X1.1
/RS485_1_DIR: IC2.2, IC2.3
/RS485_2_DIR: IC1.2, IC1.3
/SWCLK: P5.3, U1.49
/SWDIO: P5.4, U1.46
/USART1_RX: P5.6, U1.43
/USART1_TX: P5.5, U1.42
/USART2_RX: JP13.2, P4.4
/USART2_TX: JP12.2, P4.3
/USART3_RX: IC2.1, JP10.2
/USART3_TX: IC2.4, JP9.2
/USART4_RX: IC1.1, JP7.2
/USART4_TX: IC1.4, JP6.2
/USART5_RX: JP8.2, P3.4
/USART5_TX: JP11.2, P3.3
/VCAP: C11.2, U1.30
GND: C1.2, C2.2, C3.2, C4.2, C5.2, C6.2, C7.2, C8.2, C9.2, C10.2, C11.1, IC1.5, IC2.5, P1.1, P2.1, P3.1, P4.1, P5.1, P6.1, P7.1, P8.1, P11.1, R1.1, R2.1, R3.1, R4.1, R5.1, SW1.2, SW2.2, SW3.2, SW4.2, U1.12, U1.18, U1.31, U1.47, U1.63, U2.2, U2.5, U2.8, U3.2, U3.5, U3.8, U4.1, U5.1
unnamed: D1.2, R1.2
unnamed: D2.2, R2.2
unnamed: D3.2, R3.2
unnamed: D4.2, R4.2
unnamed: IC1.6, JP4.2, P8.3
unnamed: IC1.7, JP5.2, P8.4
unnamed: IC2.6, JP2.2, P11.3
unnamed: IC2.7, JP3.2, P11.4
unnamed: JP1.2, P5.2
unnamed: JP2.1, P7.3, U2.7
unnamed: JP3.1, P7.4, U2.6
unnamed: JP4.1, P6.3, U3.7
unnamed: JP5.1, P6.4, U3.6
unnamed: JP16.2, SW2.1
unnamed: JP17.2, SW3.1
unnamed: JP18.2, SW4.1

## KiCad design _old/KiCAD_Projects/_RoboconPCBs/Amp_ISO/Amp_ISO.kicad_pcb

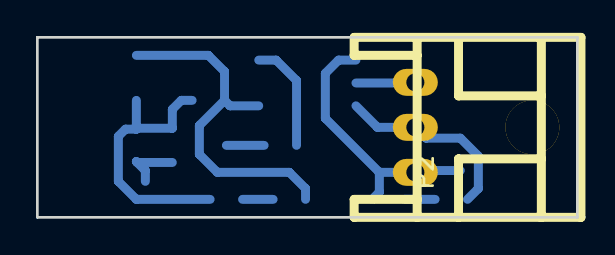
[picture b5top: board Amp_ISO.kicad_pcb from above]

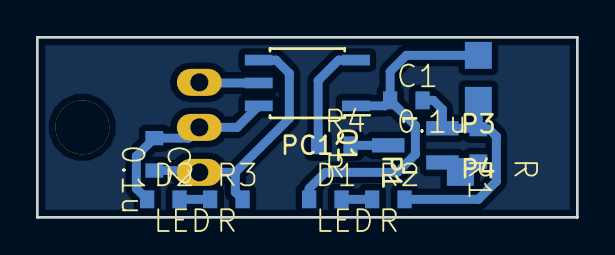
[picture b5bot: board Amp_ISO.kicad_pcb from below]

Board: 2 copper layers, 30.0 x 10.0 mm, 14 parts (13 on the bottom side), 10 nets.

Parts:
C1, C2: 0.1u; C1608_WP
D1, D2: LED; C1608_WP
P1, P3, P4: CONN_01X01; Measurement_Point_Square-SMD-Pad_Small
P2: CONN_01X03; XA_3LC
PC1: TLP117; SOIC-5_3.9x4.9mm_Pitch1.27mm
Q1: MOSFET_N; SOT-23_Handsoldering
R1, R2, R3, R4: R; C1608_WP

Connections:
/5V_LOGIC: C1.1, D1.1, P3.1, PC1.1
/5V_POWER: C2.1, D2.1, P2.2, PC1.6
/GND_LOGIC: C1.2, P4.1, Q1.S, R1.2, R2.2
/GND_POWER: C2.2, P2.1, PC1.4, R3.2
/SIGNAL_LOGIC: P1.1, Q1.G, R1.1
/SIGNAL_POWER: P2.3, PC1.5
unnamed: D1.2, R2.1
unnamed: D2.2, R3.1
unnamed: PC1.3, R4.1
unnamed: Q1.D, R4.2

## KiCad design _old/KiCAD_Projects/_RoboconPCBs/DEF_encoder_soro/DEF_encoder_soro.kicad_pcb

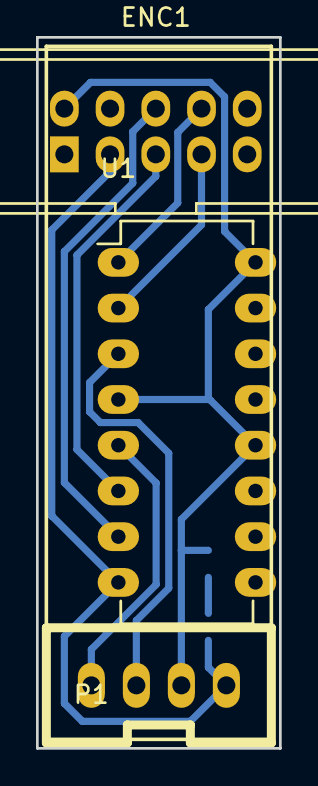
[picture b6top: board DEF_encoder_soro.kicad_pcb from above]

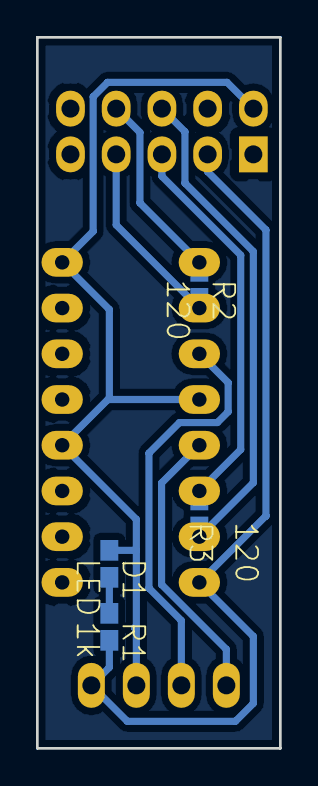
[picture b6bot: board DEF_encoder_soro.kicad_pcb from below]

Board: 2 copper layers, 13.5 x 39.5 mm, 7 parts (4 on the bottom side), 9 nets.

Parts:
D1: LED; C1608_NP
ENC1: RS422_ENCODER; DEF_ENCODER
P1: CONN_01X04; XA_4T
R1: 1k; C1608_NP
R2, R3: 120; C1608_NP
U1: SN75175; DIP-16_W7.62mm_LongPads

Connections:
+5V: D1.1, ENC1.2, P1.2, U1.4, U1.12, U1.16
/IN1_AA: ENC1.7, R2.2, U1.2
/IN1_AB: ENC1.8, R2.1, U1.1
/IN1_BA: ENC1.5, R3.2, U1.6
/IN1_BB: ENC1.6, R3.1, U1.7
/OUT1_A: P1.3, U1.3
/OUT1_B: P1.4, U1.5
GND: ENC1.3, P1.1, R1.2, U1.8
unnamed: D1.2, R1.1
